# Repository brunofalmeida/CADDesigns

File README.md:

# CAD Designs

A collection of various CAD designs I have created or experimented with (that are not part of my other repositories).

## Software

[Altium Designer](http://www.altium.com/altium-designer/overview): Electrical schematics and PCB (Printed Circuit Board) layout

[KiCad](http://kicad-pcb.org): Electrical schematics and PCB (Printed Circuit Board) layout

[SolidWorks](http://www.solidworks.com): Mechanical design and physical modelling

[SketchUp](https://www.sketchup.com): Physical modelling, sketching, and drawing

## Key Designs - UTAT (University of Toronto Aerospace Team), Space Systems division

**KiCad - pay_led** - A PCB with LEDs to control the experiment

**KiCad - pay_sensors** - A PCB with LEDs and optical sensors to control and monitor the experiment; various optical sensor designs (custom photodiode and op amp, integrated photodiode and op amp, intensity to frequency) are prototyped on this board

**SolidWorks - SliderCrank** - A constrained slider crank design; done as part of CAD training for team members

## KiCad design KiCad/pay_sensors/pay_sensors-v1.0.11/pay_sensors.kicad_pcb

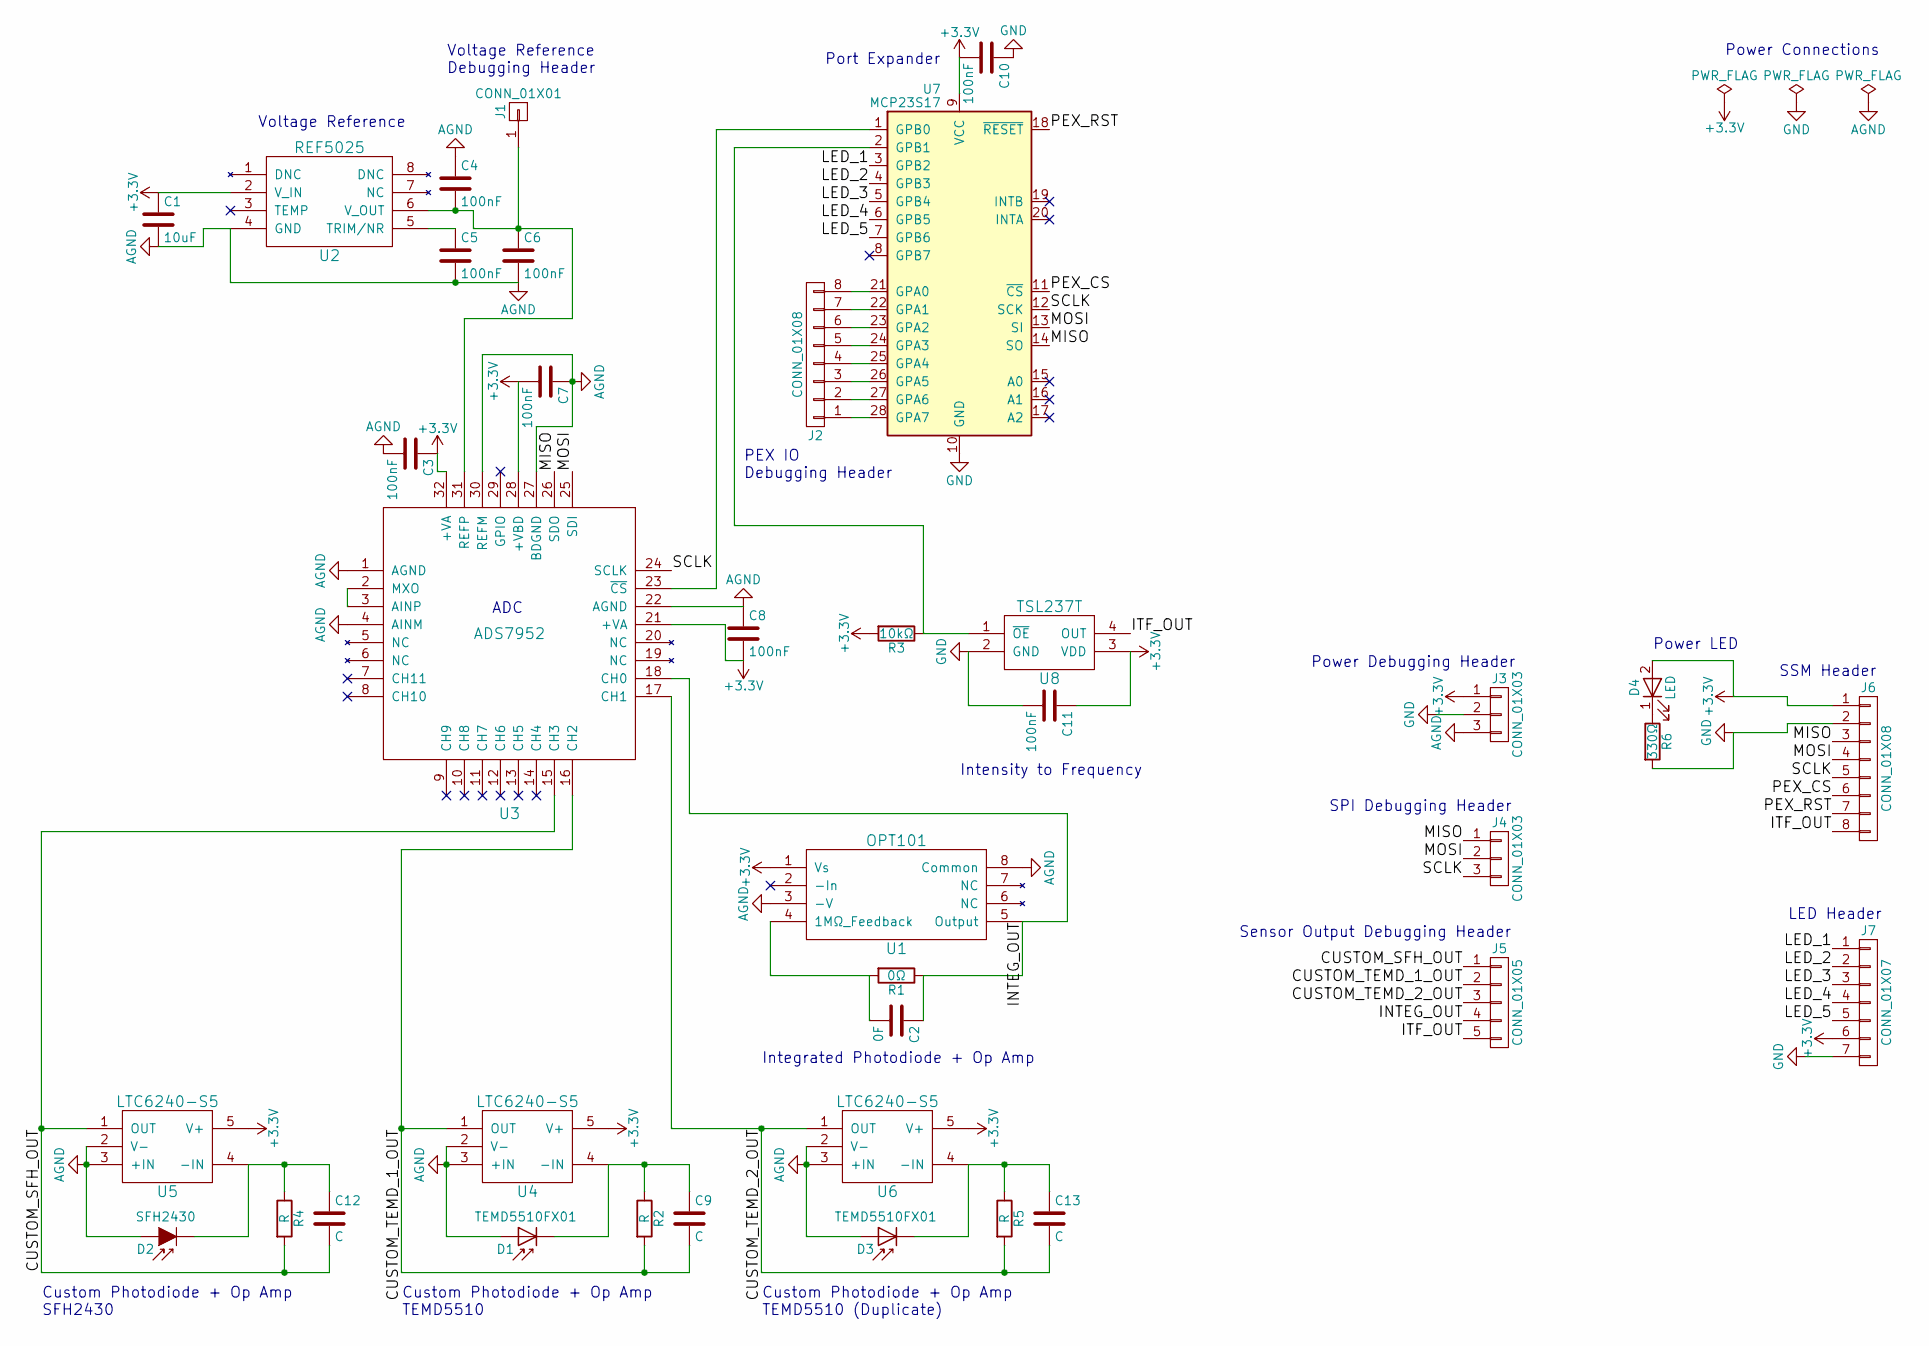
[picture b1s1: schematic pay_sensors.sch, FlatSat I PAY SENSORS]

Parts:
C1: 10uF; C_0603_HandSoldering
C2: 0F; C_0603_HandSoldering
C3, C4, C5, C6, C7, C8, C10, C11: 100nF; C_0603_HandSoldering
C9, C12, C13: C; C_0603_HandSoldering
D1, D3: TEMD5510FX01; PhotoDiode_SMD-DIL2_4.5x4
D2: SFH2430; PhotoDiode_SMD-DIL2_4.5x4
D4: LED; LED_0603_HandSoldering
J1: CONN_01X01; Pin_Header_Straight_1x01_Pitch1.27mm
J2, J6: CONN_01X08; Pin_Header_Straight_1x08_Pitch1.27mm
J3, J4: CONN_01X03; Pin_Header_Straight_1x03_Pitch1.27mm
J5: CONN_01X05; Pin_Header_Straight_1x05_Pitch1.27mm
J7: CONN_01X07; Pin_Header_Straight_1x07_Pitch1.27mm
R1: 0Ω; R_0603_HandSoldering
R2, R4, R5: R; R_0603_HandSoldering
R3: 10kΩ; R_0603_HandSoldering
R6: 330Ω; R_0603_HandSoldering
U1: OPT101; DIP-8_SMD
U2: REF5025; SOP65P490X110-8N
U3: ADS7952; QFN-32-1EP_5x5mm_Pitch0.5mm
U4, U5, U6: LTC6240-S5; SOT-23-5_HandSoldering
U7: MCP23S17; SSOP-28_5.3x10.2mm_Pitch0.65mm
U8: TSL237T; DIP-4_W7.62mm

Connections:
+3V3: C1.1, C3.1, C7.2, C8.2, C10.2, C11.1, D4.2 (A), J3.1, J6.1, J7.6, R3.2, U1.1 (Vs), U2.2 (V_IN), U3.21 (+VA), U3.28 (+VBD), U3.32 (+VA), U4.5 (V+), U5.5 (V+), U6.5 (V+), U7.9 (VCC), U8.3 (VDD)
/CUSTOM_SFH_OUT: C12.2, J5.1, R4.2, U3.15 (CH3), U5.1 (OUT)
/CUSTOM_TEMD_1_OUT: C9.2, J5.2, R2.2, U3.16 (CH2), U4.1 (OUT)
/CUSTOM_TEMD_2_OUT: C13.2, J5.3, R5.2, U3.17 (CH1), U6.1 (OUT)
/INTEG_OUT: C2.1, J5.4, R1.1, U1.5 (Output), U3.18 (CH0)
/ITF_OUT: J5.5, J6.8, U8.4 (OUT)
/LED_1: J7.1, U7.3 (GPB2)
/LED_2: J7.2, U7.4 (GPB3)
/LED_3: J7.3, U7.5 (GPB4)
/LED_4: J7.4, U7.6 (GPB5)
/LED_5: J7.5, U7.7 (GPB6)
/MISO: J4.1, J6.3, U3.26 (SDO), U7.14 (SO)
/MOSI: J4.2, J6.4, U3.25 (SDI), U7.13 (SI)
/PEX_CS: J6.6, U7.11 (~CS)
/PEX_RST: J6.7, U7.18 (~RESET)
/SCLK: J4.3, J6.5, U3.24 (SCLK), U7.12 (SCK)
AGND: C1.2, C3.2, C4.1, C5.2, C6.2, C7.1, C8.1, D1.2 (A), D2.2 (A), D3.2 (A), J3.3, U1.3 (-V), U1.8 (Common), U2.4 (GND), U3.1 (AGND), U3.4 (AINM), U3.22 (AGND), U3.27 (BDGND), U3.30 (REFM), U4.2 (V-), U4.3 (+IN), U5.2 (V-), U5.3 (+IN), U6.2 (V-), U6.3 (+IN)
GND: C10.1, C11.2, J3.2, J6.2, J7.7, R6.2, U7.10 (GND), U8.2 (GND)
unnamed: C2.2, R1.2, U1.4 (1MΩ_Feedback)
unnamed: C4.2, C6.1, J1.1, U2.6 (V_OUT), U3.31 (REFP)
unnamed: C5.1, U2.5 (TRIM/NR)
unnamed: C9.1, D1.1 (K), R2.1, U4.4 (-IN)
unnamed: C12.1, D2.1 (K), R4.1, U5.4 (-IN)
unnamed: C13.1, D3.1 (K), R5.1, U6.4 (-IN)
unnamed: D4.1 (K), R6.1
unnamed: J2.1, U7.28 (GPA7)
unnamed: J2.2, U7.27 (GPA6)
unnamed: J2.3, U7.26 (GPA5)
unnamed: J2.4, U7.25 (GPA4)
unnamed: J2.5, U7.24 (GPA3)
unnamed: J2.6, U7.23 (GPA2)
unnamed: J2.7, U7.22 (GPA1)
unnamed: J2.8, U7.21 (GPA0)
unnamed: R3.1, U7.2 (GPB1), U8.1 (~OE)
unnamed: U3.2 (MXO), U3.3 (AINP)
unnamed: U3.23 (~CS), U7.1 (GPB0)

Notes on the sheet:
Voltage Reference
ADC
Intensity to Frequency
Integrated Photodiode + Op Amp
Custom Photodiode + Op Amp TEMD5510 (Duplicate)
Custom Photodiode + Op Amp SFH2430
SSM Header
Port Expander
Power Connections
Custom Photodiode + Op Amp TEMD5510
LED Header
PEX IO Debugging Header
Sensor Output Debugging Header
SPI Debugging Header
Voltage Reference Debugging Header
Power Debugging Header
Power LED

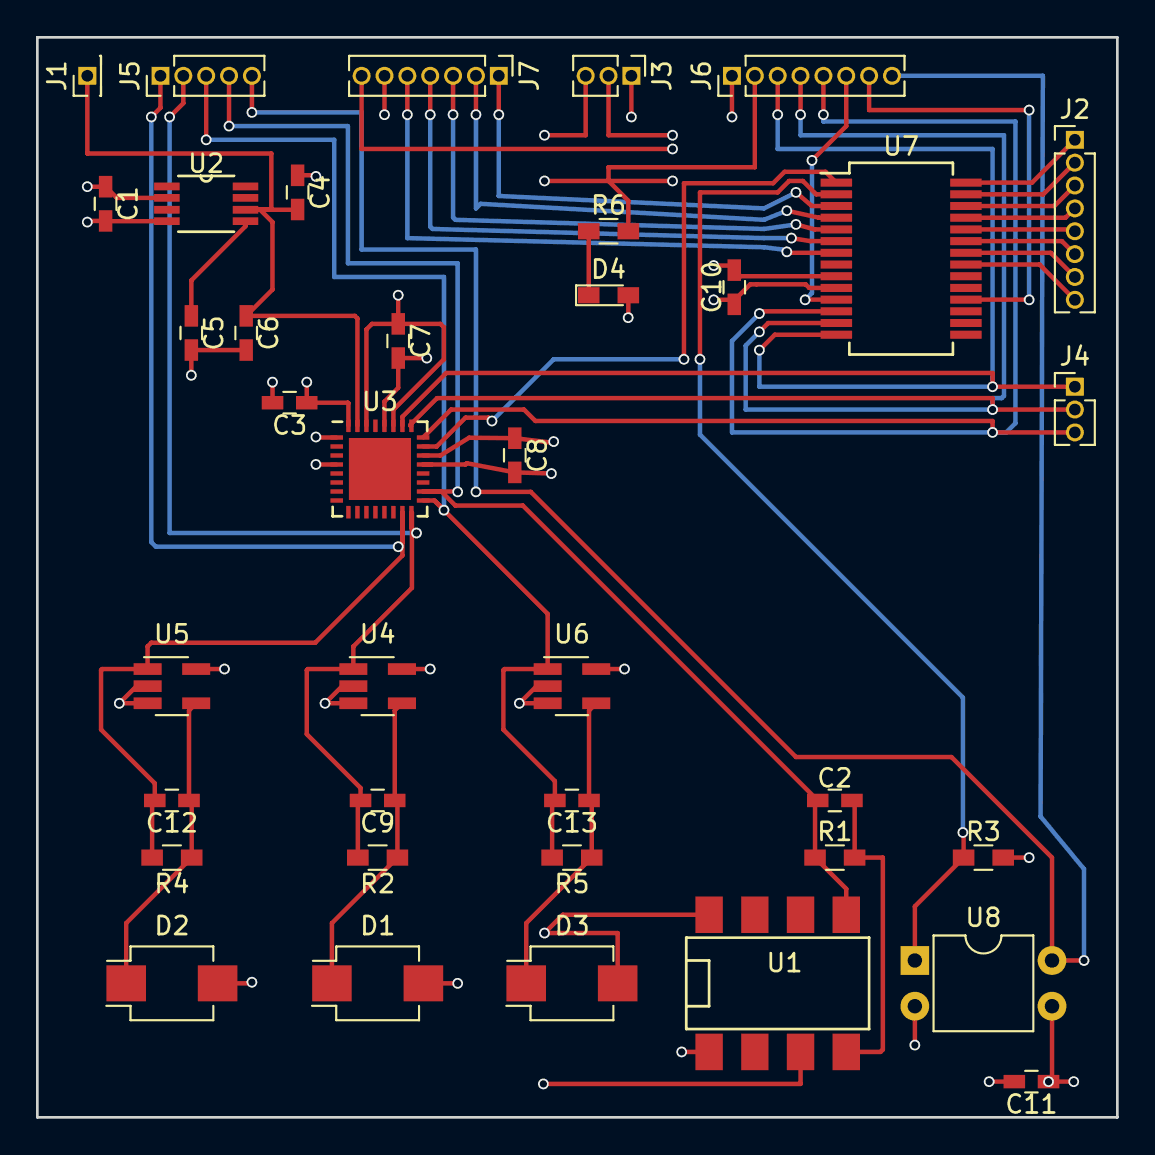
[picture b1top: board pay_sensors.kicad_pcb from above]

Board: 4 copper layers, 60.0 x 60.0 mm, 38 parts (0 on the bottom side), 36 nets.

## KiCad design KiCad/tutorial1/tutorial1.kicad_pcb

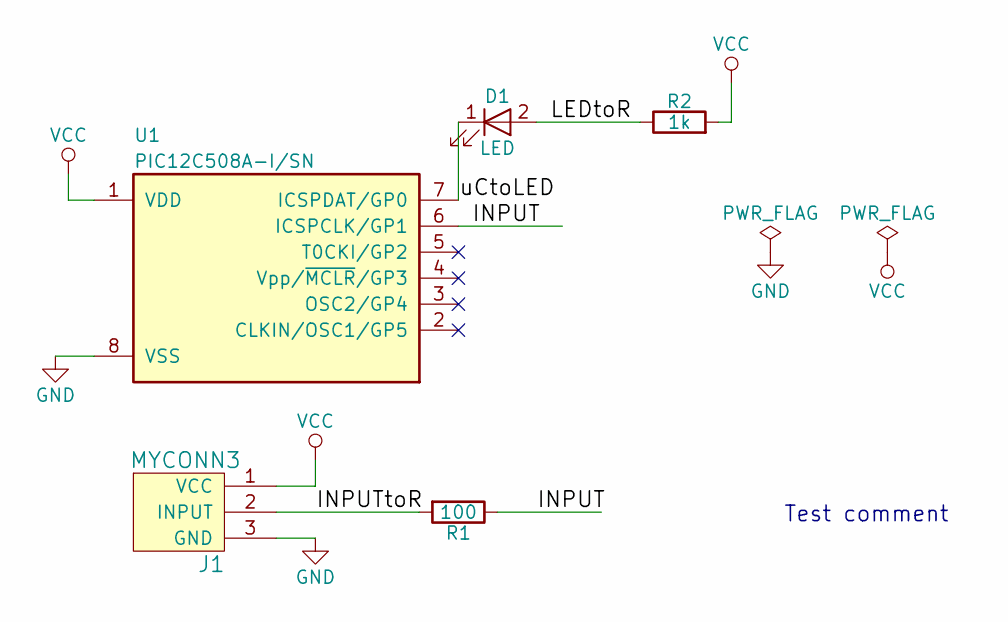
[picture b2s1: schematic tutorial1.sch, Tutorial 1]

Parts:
D1: LED; LED_D5.0mm
J1: MYCONN3; Banana_Jack_3Pin
R1: 100; R_Axial_DIN0207_L6.3mm_D2.5mm_P10.16mm_Horizontal
R2: 1k; R_Axial_DIN0207_L6.3mm_D2.5mm_P10.16mm_Horizontal
U1: PIC12C508A-I/SN; DIP-8_W7.62mm

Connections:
/INPUT: R1.1, U1.6 (ICSPCLK/GP1)
/INPUTtoR: J1.2 (INPUT), R1.2
/LEDtoR: D1.2 (A), R2.1
/uCtoLED: D1.1 (K), U1.7 (ICSPDAT/GP0)
GND: J1.3 (GND), U1.8 (VSS)
VCC: J1.1 (VCC), R2.2, U1.1 (VDD)

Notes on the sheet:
Test comment

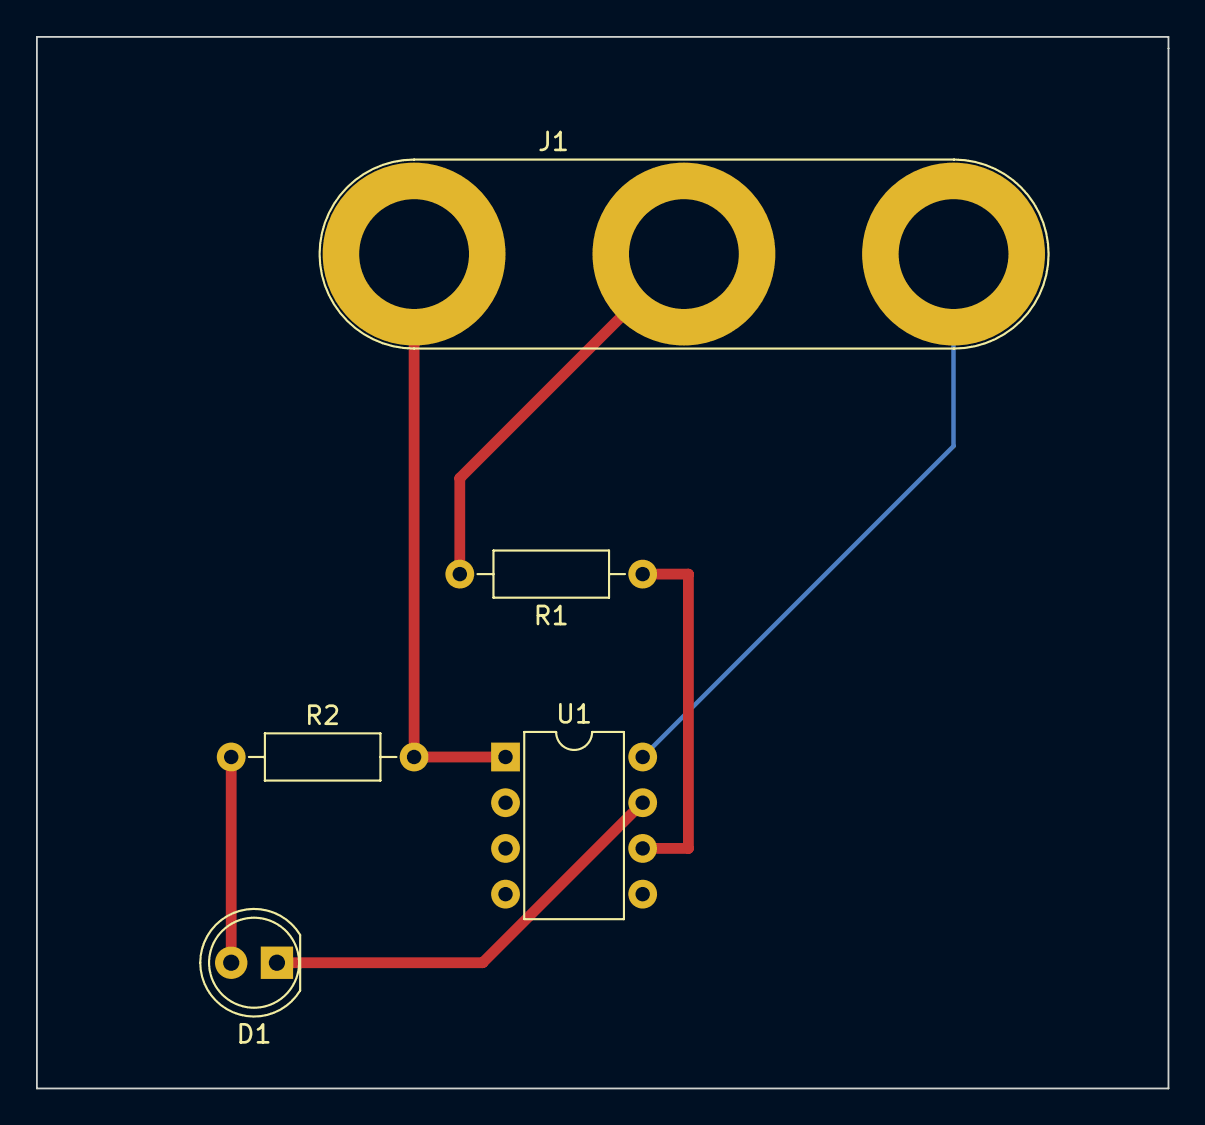
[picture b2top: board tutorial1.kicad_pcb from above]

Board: 2 copper layers, 62.9 x 58.4 mm, 5 parts (0 on the bottom side), 6 nets.

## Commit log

2017-08-28 Add SolidWorks designs
2017-08-28 Add SketchUp designs
2017-08-28 Add KiCad design
2017-08-28 Update README - software links and descriptions
2017-09-01 Add Altium Designer designs
2017-09-01 Update README - Altium Designer
2017-09-09 Add KiCad designs for UTAT sensors and LEDs
2017-10-18 Add SolidWorks slider crank
2017-10-18 Add KiCad pay_sensors (UTAT Payload sensor PCB)
2017-10-18 Update README - UTAT key designs
2017-11-26 Update README - reword main description
